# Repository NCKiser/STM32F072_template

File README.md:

This is a Kicad Template project (that also happens to be a dev-board) for the STM32F072CBT6.

***THIS PROJECT IS NOT PIN-COMPATIBLE OR PHYSICALLY COMPATIBLE WITH PROJECTS THAT USE A BLACKPILL OR ANY OTHER STM DEV-BOARD***

**THIS IS NOT A BLACKPILL OR BLUEPILL REPLACEMENT**

****See this video for turning this template into a BlackPill-compatible dev board:**** https://youtu.be/LvX-Us9VZM0

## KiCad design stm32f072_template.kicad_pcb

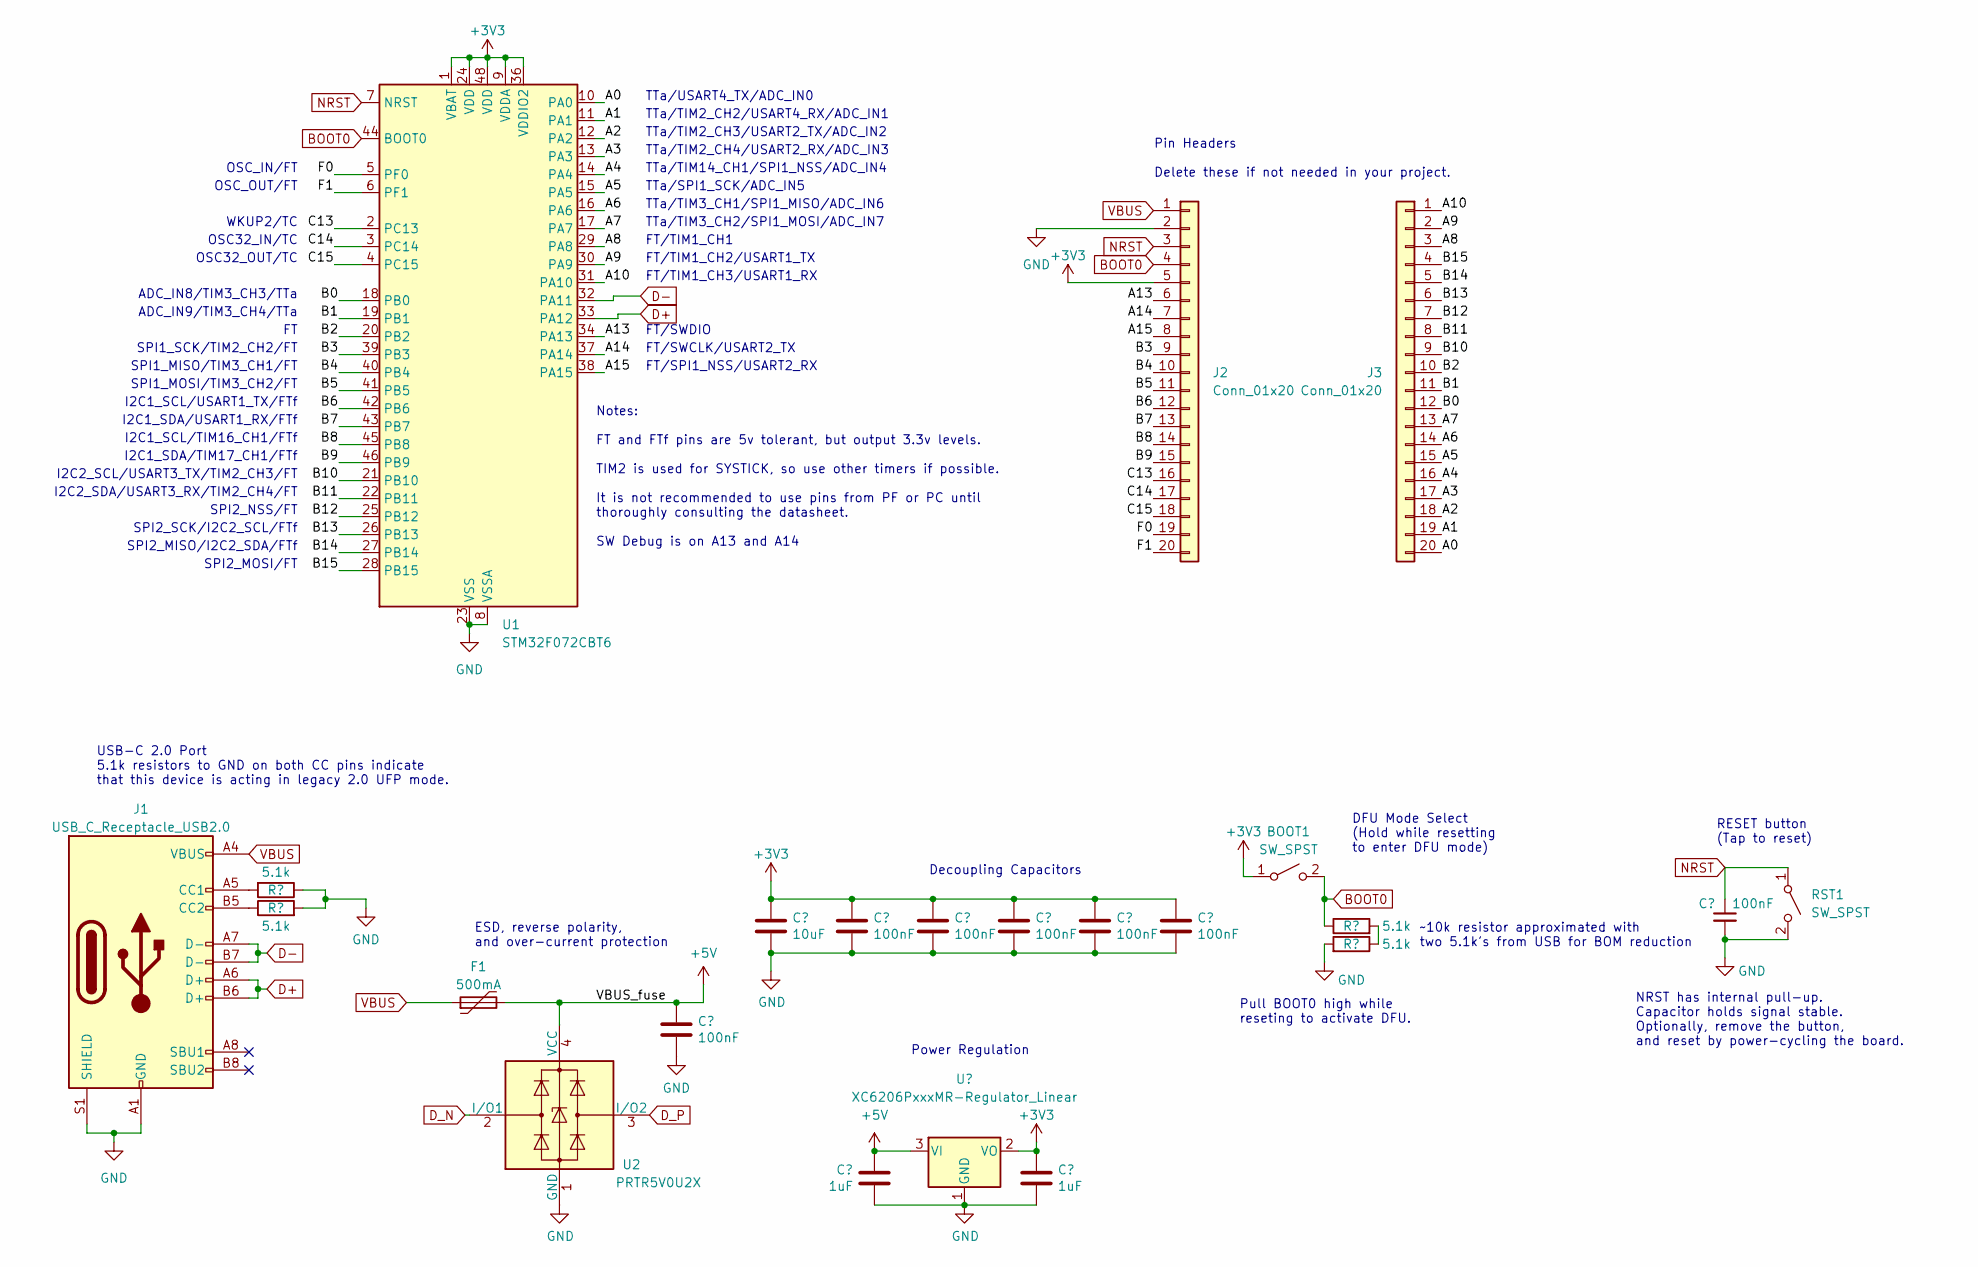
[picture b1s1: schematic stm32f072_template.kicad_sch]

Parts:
BOOT1: SW_SPST; SW_SPST_TL3342
C1, C3, C4, C5, C6, C7, C8: 100nF; C_0402_1005Metric; LCSC C307331
C2: 10uF; C_0603_1608Metric; LCSC C307331
C9, C10: 1uF; C_0402_1005Metric; LCSC C307331
F1: 500mA; Fuse_1206_3216Metric; LCSC C135341
J1: USB_C_Receptacle_USB2.0; USB_C_Receptacle_HRO_TYPE-C-31-M-12; JlcRotOffset 180
J2, J3: Conn_01x20; PinHeader_1x20_P2.54mm_Vertical
R1, R2, R3, R4: 5.1k; R_0402_1005Metric
RST1: SW_SPST; SW_SPST_TL3342
U1: STM32F072CBT6; LQFP-48_7x7mm_P0.5mm; JlcRotOffset 90
U2: PRTR5V0U2X; SOT-143; LCSC C2827688
U3: XC6206PxxxMR-Regulator_Linear; SOT-23; LCSC C5446

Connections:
+3V3: BOOT1.1 (A), C2.1, C3.1, C4.1, C5.1, C6.1, C7.1, C10.1, J2.5, U1.1 (VBAT), U1.9 (VDDA), U1.24 (VDD), U1.36 (VDDIO2), U1.48 (VDD), U3.2 (VO)
+5V: C8.1, C9.1, F1.2, U2.4 (VCC), U3.3 (VI)
/A0: J3.20, U1.10 (PA0)
/A1: J3.19, U1.11 (PA1)
/A2: J3.18, U1.12 (PA2)
/A3: J3.17, U1.13 (PA3)
/A4: J3.16, U1.14 (PA4)
/A5: J3.15, U1.15 (PA5)
/A6: J3.14, U1.16 (PA6)
/A7: J3.13, U1.17 (PA7)
/A8: J3.3, U1.29 (PA8)
/A9: J3.2, U1.30 (PA9)
/A10: J3.1, U1.31 (PA10)
/A13: J2.6, U1.34 (PA13)
/A14: J2.7, U1.37 (PA14)
/A15: J2.8, U1.38 (PA15)
/B0: J3.12, U1.18 (PB0)
/B1: J3.11, U1.19 (PB1)
/B2: J3.10, U1.20 (PB2)
/B3: J2.9, U1.39 (PB3)
/B4: J2.10, U1.40 (PB4)
/B5: J2.11, U1.41 (PB5)
/B6: J2.12, U1.42 (PB6)
/B7: J2.13, U1.43 (PB7)
/B8: J2.14, U1.45 (PB8)
/B9: J2.15, U1.46 (PB9)
/B10: J3.9, U1.21 (PB10)
/B11: J3.8, U1.22 (PB11)
/B12: J3.7, U1.25 (PB12)
/B13: J3.6, U1.26 (PB13)
/B14: J3.5, U1.27 (PB14)
/B15: J3.4, U1.28 (PB15)
/C13: J2.16, U1.2 (PC13)
/C14: J2.17, U1.3 (PC14)
/C15: J2.18, U1.4 (PC15)
/F0: J2.19, U1.5 (PF0)
/F1: J2.20, U1.6 (PF1)
BOOT0: BOOT1.2 (B), J2.4, R3.1, U1.44 (BOOT0)
D+: J1.A6 (D+), J1.B6 (D+), U1.33 (PA12)
D-: J1.A7 (D-), J1.B7 (D-), U1.32 (PA11)
D_N: U2.2 (I/O1)
D_P: U2.3 (I/O2)
GND: C1.2, C2.2, C3.2, C4.2, C5.2, C6.2, C7.2, C8.2, C9.2, C10.2, J1.A1 (GND), J1.A12 (GND), J1.B1 (GND), J1.B12 (GND), J1.S1 (SHIELD), J2.2, R1.1, R2.2, R4.2, RST1.2 (B), U1.8 (VSSA), U1.23 (VSS), U1.35 (VSS), U1.47 (VSS), U2.1 (GND), U3.1 (GND)
NRST: C1.1, J2.3, RST1.1 (A), U1.7 (NRST)
unnamed: J1.A5 (CC1), R1.2
unnamed: J1.B5 (CC2), R2.1
unnamed: R3.2, R4.1
VBUS: F1.1, J1.A4 (VBUS), J1.A9 (VBUS), J1.B4 (VBUS), J1.B9 (VBUS), J2.1

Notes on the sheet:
SPI1_SCK/TIM2_CH2/FT
Pin Headers Delete these if not needed in your project.
FT/TIM1_CH1
FT/TIM1_CH3/USART1_RX
SPI2_NSS/FT
Notes: FT and FTf pins are 5v tolerant, but output 3.3v levels. TIM2 is used for SYSTICK, so use other timers if possible. It is not recommended to use pins from PF or PC until thoroughly consulting the datasheet. SW Debug is on A13 and A14
TTa/TIM2_CH4/USART2_RX/ADC_IN3
NRST has internal pull-up. Capacitor holds signal stable. Optionally, remove the button, and reset by power-cycling the board.
FT/SWDIO
Decoupling Capacitors
SPI1_MOSI/TIM3_CH2/FT
ADC_IN9/TIM3_CH4/TTa
I2C2_SCL/USART3_TX/TIM2_CH3/FT
SPI2_MISO/I2C2_SDA/FTf
FT/SWCLK/USART2_TX
I2C1_SCL/TIM16_CH1/FTf
~10k resistor approximated with two 5.1k's from USB for BOM reduction
TTa/TIM2_CH2/USART4_RX/ADC_IN1
USB-C 2.0 Port 5.1k resistors to GND on both CC pins indicate that this device is acting in legacy 2.0 UFP mode.
TTa/TIM2_CH3/USART2_TX/ADC_IN2
OSC_IN/FT
DFU Mode Select (Hold while resetting to enter DFU mode)
WKUP2/TC
I2C2_SDA/USART3_RX/TIM2_CH4/FT
ADC_IN8/TIM3_CH3/TTa
RESET button (Tap to reset)
Pull BOOT0 high while reseting to activate DFU.
I2C1_SDA/TIM17_CH1/FTf
TTa/SPI1_SCK/ADC_IN5
TTa/TIM3_CH1/SPI1_MISO/ADC_IN6
TTa/TIM3_CH2/SPI1_MOSI/ADC_IN7
OSC32_OUT/TC
FT/SPI1_NSS/USART2_RX
SPI1_MISO/TIM3_CH1/FT
OSC32_IN/TC
TTa/TIM14_CH1/SPI1_NSS/ADC_IN4
I2C1_SDA/USART1_RX/FTf
SPI2_MOSI/FT
FT/TIM1_CH2/USART1_TX
Power Regulation

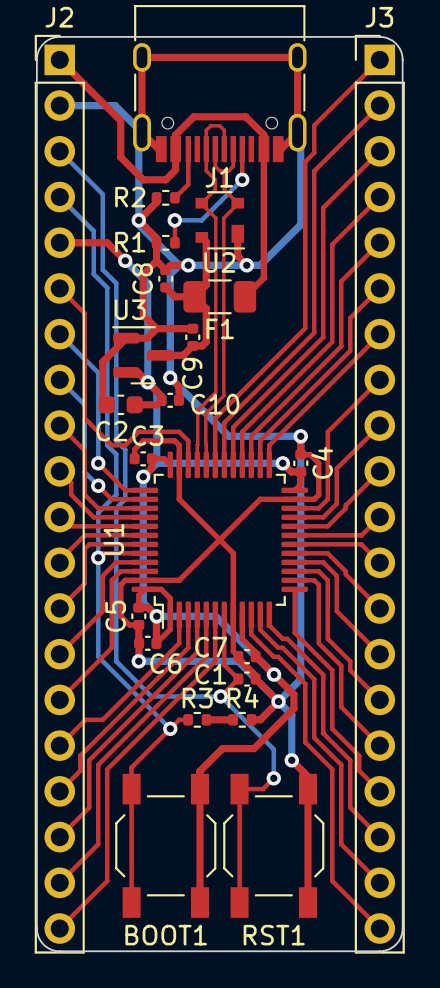
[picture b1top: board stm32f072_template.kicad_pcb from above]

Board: 2 copper layers, 20.3 x 50.8 mm, 23 parts (0 on the bottom side), 46 nets.

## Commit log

2024-01-31 Created STM32 template
2024-01-31 Fixed net typos, added notes
2024-02-01 Create LICENCE
